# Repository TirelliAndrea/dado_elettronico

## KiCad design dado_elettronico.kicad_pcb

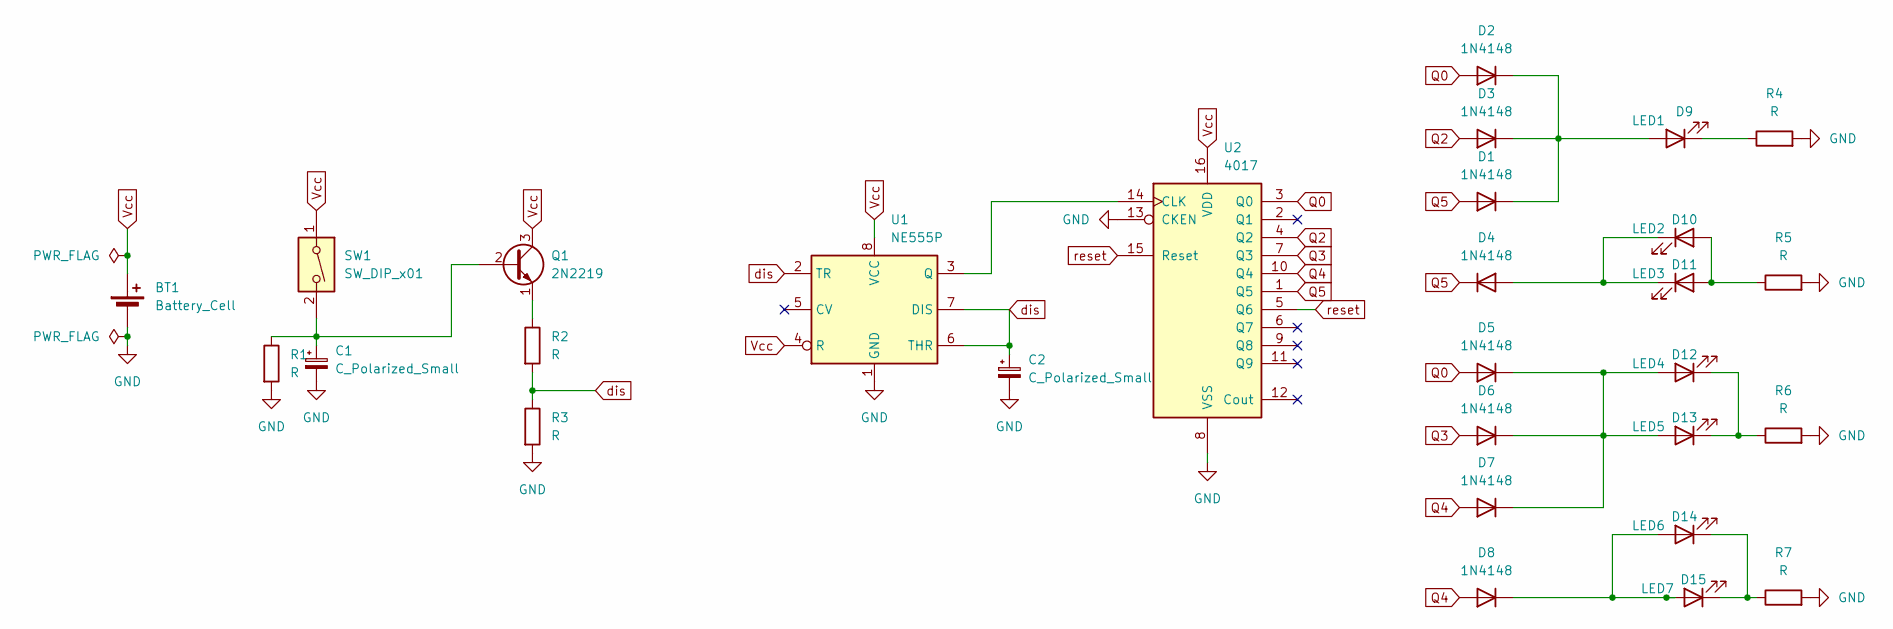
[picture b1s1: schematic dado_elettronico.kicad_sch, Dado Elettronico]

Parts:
BT1: Battery_Cell; BatteryHolder_Keystone_1057_1x2032
C1, C2: C_Polarized_Small; CP_Radial_D5.0mm_P2.50mm
D1, D2, D3, D4, D5, D6, D7, D8: 1N4148; D_DO-35_SOD27_P7.62mm_Horizontal
D9: LED1; LED_D4.0mm
D10: LED2; LED_D4.0mm
D11: LED3; LED_D4.0mm
D12: LED4; LED_D4.0mm
D13: LED5; LED_D4.0mm
D14: LED6; LED_D4.0mm
D15: LED7; LED_D4.0mm
Q1: 2N2219; TO92_S9014_127P510H650-3
R1, R2, R3, R4, R5, R6, R7: R; R_Axial_DIN0204_L3.6mm_D1.6mm_P5.08mm_Horizontal
SW1: SW_DIP_x01; SW_DIP_SPSTx01_Slide_9.78x4.72mm_W7.62mm_P2.54mm
U1: NE555P; DIP-8_W7.62mm
U2: 4017; DIP-16_W7.62mm_Socket

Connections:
GND: BT1.2 (-), C1.2, C2.2, R1.2, R3.2, R4.2, R5.2, R6.2, R7.2, U1.1 (GND), U2.8 (VSS), U2.13 (CKEN)
unnamed: D1.1 (K), D2.1 (K), D3.1 (K), D9.2 (A)
unnamed: D9.1 (K), R4.1
unnamed: D10.2 (A), D11.2 (A), R5.1
unnamed: D4.2 (A), D10.1 (K), D11.1 (K)
unnamed: D5.1 (K), D6.1 (K), D7.1 (K), D12.2 (A), D13.2 (A)
unnamed: D12.1 (K), D13.1 (K), R6.1
unnamed: D8.1 (K), D14.2 (A), D15.2 (A)
unnamed: D14.1 (K), D15.1 (K), R7.1
unnamed: C1.1, Q1.2 (B), R1.1, SW1.2
unnamed: Q1.1 (E), R2.1
unnamed: U1.3 (Q), U2.14 (CLK)
Q0: D2.2 (A), D5.2 (A), U2.3 (Q0)
Q2: D3.2 (A), U2.4 (Q2)
Q3: D6.2 (A), U2.7 (Q3)
Q4: D7.2 (A), D8.2 (A), U2.10 (Q4)
Q5: D1.2 (A), D4.1 (K), U2.1 (Q5)
Vcc: BT1.1 (+), Q1.3 (C), SW1.1, U1.4 (R), U1.8 (VCC), U2.16 (VDD)
dis: C2.1, R2.2, R3.1, U1.2 (TR), U1.6 (THR), U1.7 (DIS)
reset: U2.5 (Q6), U2.15 (Reset)

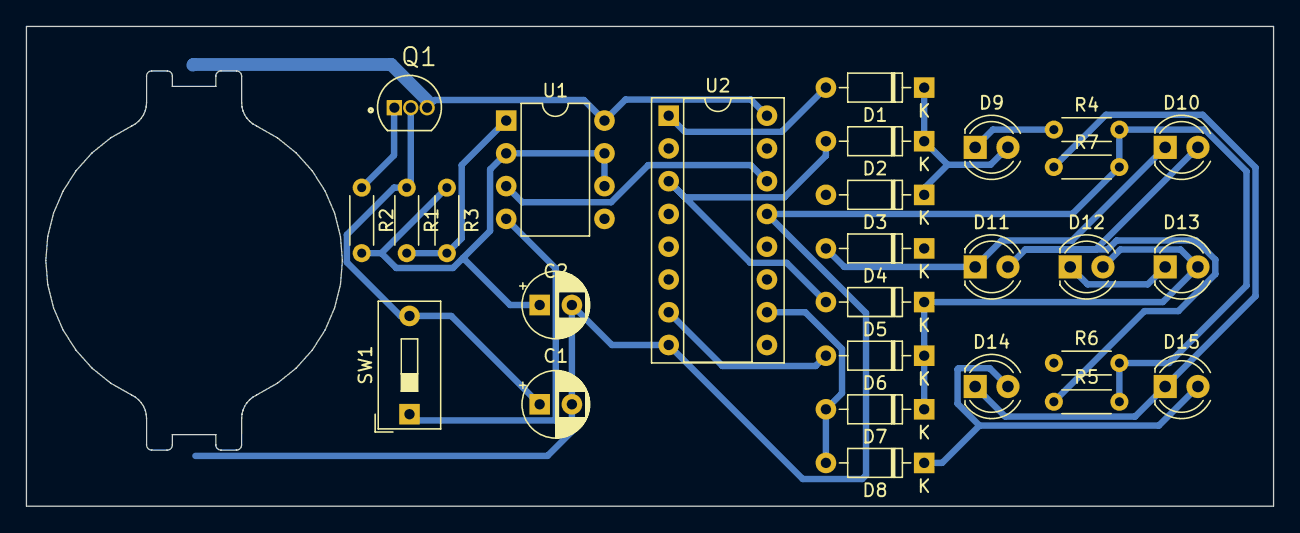
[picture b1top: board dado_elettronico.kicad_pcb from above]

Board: 2 copper layers, 96.7 x 37.2 mm, 29 parts (1 on the bottom side), 20 nets.

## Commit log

2024-10-12 aggiunto componenti
    Aggiunto componenti
2024-10-13 collegamento del contatore con i diodi
2024-10-27 schema elettrico completo
    schema elettrico completo senza impronta componenti
2024-10-27 schema elettrico con impronte
    assegnate impronte ai componenti
2024-10-28 aggiunta impronta transistor e posizionato componenti
2024-11-01 sbroglio per test incisione
